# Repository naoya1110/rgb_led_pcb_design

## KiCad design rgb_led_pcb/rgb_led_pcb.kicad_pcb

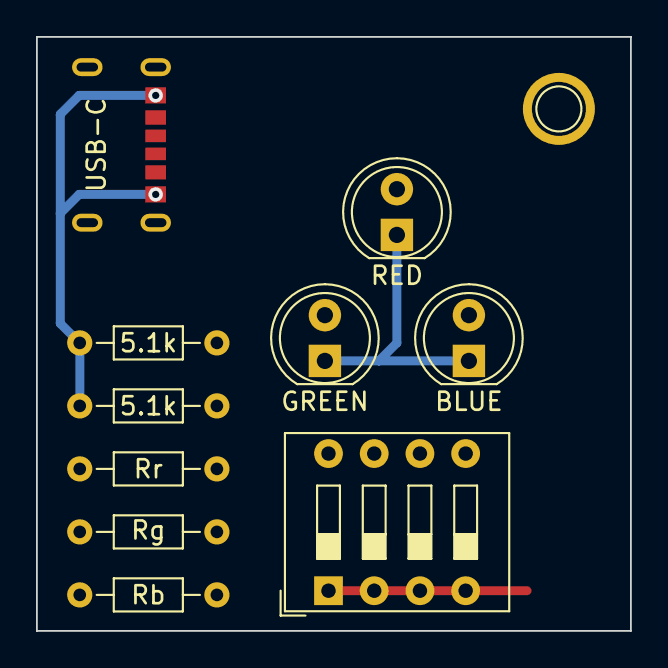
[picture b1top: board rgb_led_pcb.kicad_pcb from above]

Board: 2 copper layers, 33.0 x 33.0 mm, 10 parts (0 on the bottom side), 10 nets.

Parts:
BLUE: Blue; LED_D5.0mm
GREEN: Green; LED_D5.0mm
R1, R2: 5.1k; R_Axial_DIN0204_L3.6mm_D1.6mm_P7.62mm_Horizontal
RED: Red; LED_D5.0mm
Rb: R; R_Axial_DIN0204_L3.6mm_D1.6mm_P7.62mm_Horizontal
Rg: R; R_Axial_DIN0204_L3.6mm_D1.6mm_P7.62mm_Horizontal
Rr: R; R_Axial_DIN0204_L3.6mm_D1.6mm_P7.62mm_Horizontal
SW: SW_DIP_x04; SW_DIP_SPSTx04_Slide_9.78x12.34mm_W7.62mm_P2.54mm
USB-C: USB_C_Receptacle_PowerOnly_6P; UJC-HP-3-SMT-TR

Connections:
+5V: SW.1, SW.2, SW.3, SW.4, USB-C.A9 (VBUS), USB-C.B9 (VBUS)
GND: BLUE.1 (K), GREEN.1 (K), R1.2, R2.2, RED.1 (K), USB-C.A12 (GND), USB-C.B12 (GND)
unnamed: R2.1, USB-C.A5 (CC1)
unnamed: R1.1, USB-C.B5 (CC2)
unnamed: RED.2 (A), Rr.2
unnamed: GREEN.2 (A), Rg.2
unnamed: BLUE.2 (A), Rb.2
unnamed: Rr.1, SW.6
unnamed: Rg.1, SW.7
unnamed: Rb.1, SW.8
